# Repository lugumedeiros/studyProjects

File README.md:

# studyProjects
This is a compilation for all my projects from college or courses.

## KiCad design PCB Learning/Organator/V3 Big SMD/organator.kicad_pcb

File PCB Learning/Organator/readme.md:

## Printed Version
I wanted **V3** to be printed, but I made a mistake while moving my files and got this version. This is a previous version of to the **V2** available here, it has almost the same components, where the biggest difference is that the newer version uses a SMD battery holder instead.

I made sure to have a little hole on the border to use this toy as a keychain, due to the size, and even though I didn't assembled it, I think it ended really nice.

## V1 - PTH Version
This was the first version I made from a course I was watching on Udemy, it's very similar to the one created by the teacher and it has only PTH components.

This version uses a simple LDO to 5V, NPN Amplifier and a 555 Generic Counter. It has a 9V battery package slot but it can be used any other battery over 5V, it will mainly depend on the LDO properties.

## V2 - SMD
This is the final stage of my current SMD version I want to send to production. This version doesn't have a LDO due to being made for a CR2032 battery, the 555 counter was changed to a CMOS one for the low voltage supplied.

My initial idea was to make a puzzle style pcb where each piece would have a different frequency for different sounds, and it would be possible to assemble 3 different pieces together like a puzzle game, creating then a bigger toy. I fastly turned down the idea of printing all PCB due my unstable financial situation at the moment, in the end it was a mistake due the enourmous taxes and delivery I paid which would made no difference.

This is an older version, but has the same concept

## V3 - SMD
This is almost the same as the V2, but with bigger packages for easier manual soldering. Assembly is hella expensive :(
obs.: There's a mistake in the 2 capacitors footprints.

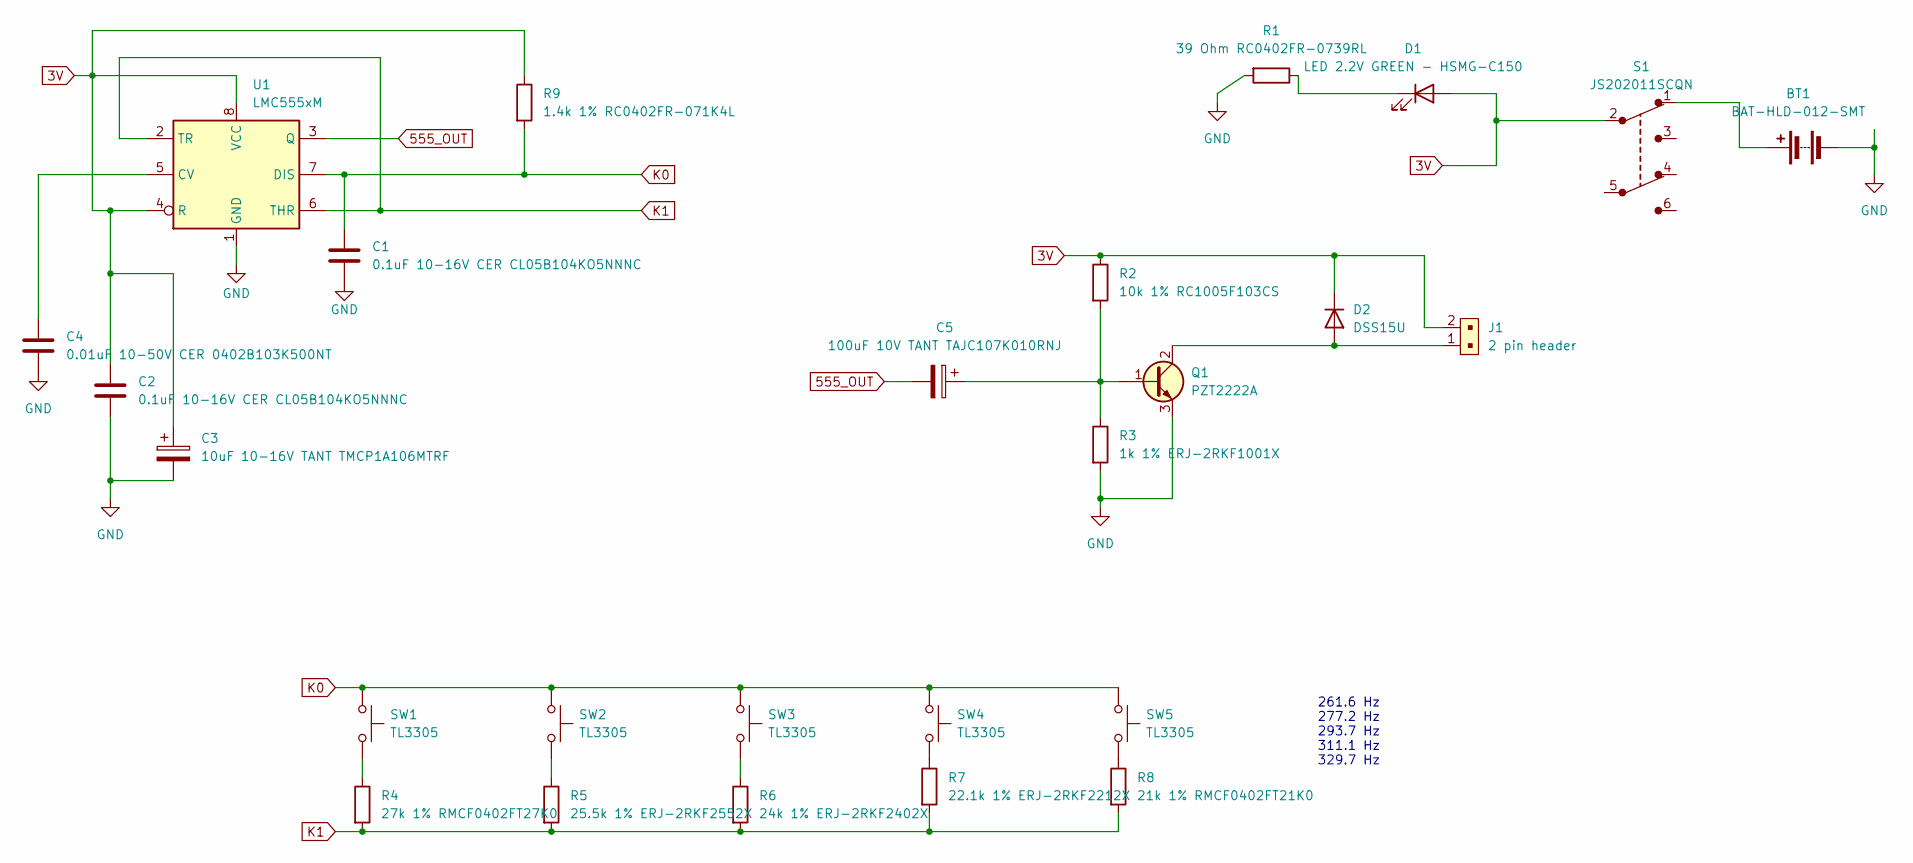
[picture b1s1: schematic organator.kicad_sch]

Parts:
BT1: BAT-HLD-012-SMT; BatteryHolder_LINX_BAT-HLD-012-SMT
C1, C2: 0.1uF 10-16V CER CL05B104KO5NNNC; C_0402_1005Metric
C3: 10uF 10-16V TANT TMCP1A106MTRF; CP_EIA-2012-12_Kemet-R
C4: 0.01uF 10-50V CER 0402B103K500NT; C_0402_1005Metric
C5: 100uF 10V TANT TAJC107K010RNJ; CP_EIA-6032-15_Kemet-U
D1: LED 2.2V GREEN - HSMG-C150; LED_1206_3216Metric_Pad1.42x1.75mm_HandSolder
D2: DSS15U; D_SOD-123
J1: 2 pin header; PinHeader_1x2_P2.54mm_Drill1.02mm; MPN 22-23-2021; Digi-Key_PN WM4200-ND
Q1: PZT2222A; SOT-223-3_TabPin2
R1: 39 Ohm RC0402FR-0739RL; R_0402_1005Metric
R2: 10k 1% RC1005F103CS; R_0402_1005Metric
R3: 1k 1% ERJ-2RKF1001X; R_0402_1005Metric
R4: 27k 1% RMCF0402FT27K0; R_0402_1005Metric
R5: 25.5k 1% ERJ-2RKF2552X; R_0402_1005Metric
R6: 24k 1% ERJ-2RKF2402X; R_0402_1005Metric
R7: 22.1k 1% ERJ-2RKF2212X; R_0402_1005Metric
R8: 21k 1% RMCF0402FT21K0; R_0402_1005Metric
R9: 1.4k 1% RC0402FR-071K4L; R_0402_1005Metric
S1: JS202011SCQN; Switch_Slide_JS202011SCQN; MPN JS202011SCQN; Digi-Key_PN 401-2002-1-ND
SW1, SW2, SW3, SW4, SW5: TL3305; SW_SPST_TL3305B
U1: LMC555xM; SOIC-8_3.9x4.9mm_P1.27mm

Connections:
3V: C2.1, C3.1, D1.2 (A), D2.1 (K), J1.2, R2.1, R9.1, S1.2, U1.4 (R), U1.8 (VCC)
555_OUT: C5.2, U1.3 (Q)
GND: BT1.2 (-), C1.2, C2.2, C3.2, C4.2, Q1.3 (E), R1.2, R3.2, U1.1 (GND)
K0: C1.1, R9.2, SW1.1, SW2.1, SW3.1, SW4.1, SW5.1, U1.7 (DIS)
K1: R4.2, R5.2, R6.2, R7.2, R8.2, U1.2 (TR), U1.6 (THR)
unnamed: BT1.1 (+), S1.1
unnamed: D1.1 (K), R1.1
unnamed: D2.2 (A), J1.1, Q1.2 (C)
unnamed: C5.1, Q1.1 (B), R2.2, R3.1
unnamed: R4.1, SW1.2
unnamed: R5.1, SW2.2
unnamed: R6.1, SW3.2
unnamed: R7.1, SW4.2
unnamed: R8.1, SW5.2
unnamed: C4.1, U1.5 (CV)

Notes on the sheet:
261.6 Hz 277.2 Hz 293.7 Hz 311.1 Hz 329.7 Hz

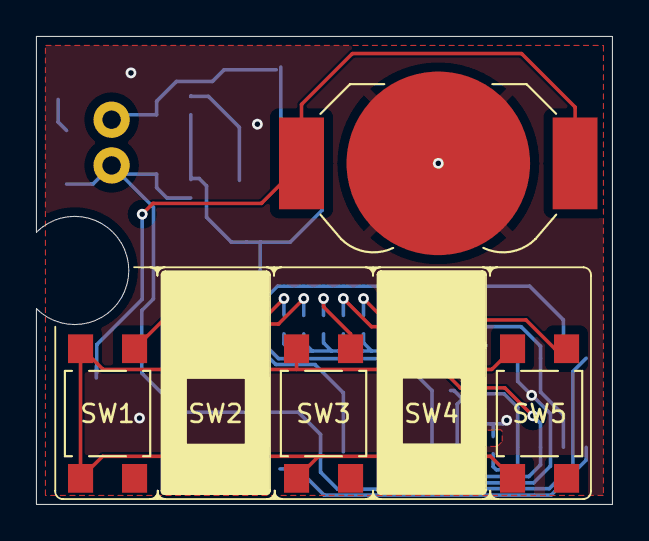
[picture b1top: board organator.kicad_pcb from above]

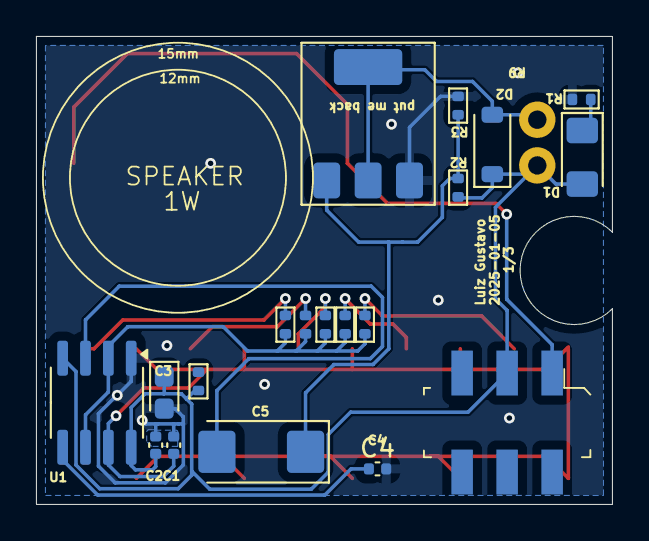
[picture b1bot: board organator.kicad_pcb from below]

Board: 2 copper layers, 32.0 x 26.0 mm, 26 parts (20 on the bottom side), 15 nets.

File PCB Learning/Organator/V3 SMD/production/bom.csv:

Designator,Footprint,Quantity,Value,LCSC Part #
BT1,BatteryHolder_LINX_BAT-HLD-012-SMT,1,BAT-HLD-012-SMT,
"C1, C2",0402,2,0.1uF 10-16V CER CL05B104KO5NNNC,
C3,CP_EIA-2012-12_Kemet-R,1,10uF 10-16V TANT TMCP1A106MTRF,
C4,0402,1,0.01uF 10-50V CER 0402B103K500NT,
C5,CP_EIA-6032-15_Kemet-U,1,100uF 10V TANT TAJC107K010RNJ,
D1,1206,1,LED 2.2V GREEN - HSMG-C150,
D2,D_SOD-123,1,DSS15U,
J1,PinHeader_1x2_P2.54mm_Drill1.02mm,1,2 pin header,22-23-2021
Q1,SOT-223-3_TabPin2,1,PZT2222A,
R1,0402,1,39 Ohm RC0402FR-0739RL,
R2,0402,1,10k 1% RC1005F103CS,
R3,0402,1,1k 1% ERJ-2RKF1001X,
R4,0402,1,27k 1% RMCF0402FT27K0,
R5,0402,1,25.5k 1% ERJ-2RKF2552X,
R6,0402,1,24k 1% ERJ-2RKF2402X,
R7,0402,1,22.1k 1% ERJ-2RKF2212X,
R8,0402,1,21k 1% RMCF0402FT21K0,
R9,0402,1,1.4k 1% RC0402FR-071K4L,
S1,Switch_Slide_JS202011SCQN,1,JS202011SCQN,JS202011SCQN
"SW1, SW2, SW3, SW4, SW5",SW_SPST_TL3305B,5,TL3305,
U1,SOIC-8_3.9x4.9mm_P1.27mm,1,LMC555xM,

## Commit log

2023-08-19 Create SE_IMC
2023-08-19 Rename SE_IMC to SE_IMC.py
2023-08-19 Update 100DBootCamp_PasswordGenerator.py
    I forgot to pass password as string. Fixed!
2023-08-21 Rename SE_IMC.py to Anhanguera/SE_IMC.py
2023-08-21 Rename 100DBootCamp_PasswordGenerator.py to 100 Days Python/PasswordGenerator.py
2023-08-21 Rename 100DBootCamp_rockPaperScissors.py to 100 Days Python/rockPaperScissors.py
2023-08-23 Rename 100 Days Python/rockPaperScissors.py to 100 Days Python/RockPaperScissors/rockPaperScissors.py
2023-08-23 Rename 100 Days Python/Caesar Cipher.py to 100 Days Python/Caesar Cipher/Caesar Cipher.py
2023-08-23 Rename 100 Days Python/PasswordGenerator.py to 100 Days Python/PasswordGenerator/PasswordGenerator.py
2023-08-23 Rename 100 Days Python/Secret Auction.py to 100 Days Python/Secret Auction/Secret Auction.py
2023-08-23 hangman FlowChart
2023-09-23 Rename CPP/Calendar_for_any_year.cpp to CPP/Calendar_for_any_year/Calendar_for_any_year.cpp
2023-09-23 Rename CPP/README.txt to CPP/Calendar_for_any_year/README.txt
2025-01-11 Small Version added
2025-01-12 dir name changed
2025-02-10 feb/2025 update
2025-02-10 update feb 2025
2025-03-01 ASL training models test
2025-03-27 quicksrot and mergesort
2025-03-29 Add BFS search implementations
2025-03-29 Implement Dijkstra's algorithm (bad)
2025-03-30 Implement multiple versions of Dijkstra's algorithm and add a function to generate a large random graph for testing
2025-04-05 Add insertion sort
2025-04-07 Refactor sorting and searching algorithms into class methods; add binary search
2025-04-12 Refactor merge_sort method to use class method; add findCrossoverIndex and integerCubeRoot methods with binary search implementation
2025-04-13 Changed folder, add Heap Class
2025-04-13 changed folder
2025-04-15 Modify MinHeap to be a value class instead
2025-04-15 add maxheap
2025-04-17 add heapsort, heapmedian
2025-04-17 fix medianheap
2025-04-19 change quicksort from Size:nlogn to Size:n
2025-04-23 Now Quicksort has 2 implementations one with Size(logn) abd tge "better" with size (n). I had some problems with the previous versions, so I made another one more in my thinking style. Add quick_sele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
2025-04-24 fix quicksort
2025-05-01 Add binary search tree and hash
